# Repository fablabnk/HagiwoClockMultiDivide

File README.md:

This is an attempt to make a PCB version of [Hagiwo's Clock Multi Divide module](https://note.com/solder_state/n/n8907f2f6e8f5).

# Notes / ToDo

- I'm using the schematic symbol for Arduino Nano v3.x, check that this matches my actual Nano
- Change pin order of Eurocad 2x5 pin power symbol
- Update screw hole positions on panel template - mine fall between two rail screw holes
    - centre is: 3mm down from edge, 5.08mm across from edge, 3.2 in diameter, seems correct

## Diodes and voltage protection

Which diodes protect against which things? Original text says that the circuit:
1. Does not break due to overvoltage
2. Does not break due to negative voltage
3. Does not break due to overcurrent
4. External clock does not enter the internal clock output
5. Internal clock output does not enter the external clock input
But which diodes do which things?

These diodes are there for protecting the arduino if you plug something in that sends voltages it can’t handle.
Everything negative will go to ground thru one set of diodes, everything over 5V will go to the 5V rail thru the other set.
Out has only one diode because there is already one on pin D13.

## Power

- Arduino is given VIN of 12V? Or is it somehow powered from the 5V rail?
- I notice Higawo uses a 16 pin connector
- But Arduino Nano operating range is quoted as 7-12V
- Should we connect capacitors to the +-12V power connector rails?

## Updating the schematic

There were some small issues with the original Hagiwo schematic. I made the following changes in my KiCad schematic:
- in the External Clock In section, there should be a dot connecting two vertical BAT43 diodes
According to the discussion [here](https://lookmumnocomputer.discourse.group/t/arduino-clock-multiple-divider/2612/3), for the Master Clock Out section:
- The initial diode after Arduino pin D13 should be a small signal diode (IN4148 or similiar)
- The SchottKey diode following the 470 Ohm resistor should actually come before the resistor

## PCB Issues

- My SPDT switch is not board mountable and will need to be wired to the board instead. So I used the footprint "TerminalBlock:TerminalBlock_bornier-3_P5.08mm"
- The Arduino nano will be mounted to the front of the PCB using pin headers

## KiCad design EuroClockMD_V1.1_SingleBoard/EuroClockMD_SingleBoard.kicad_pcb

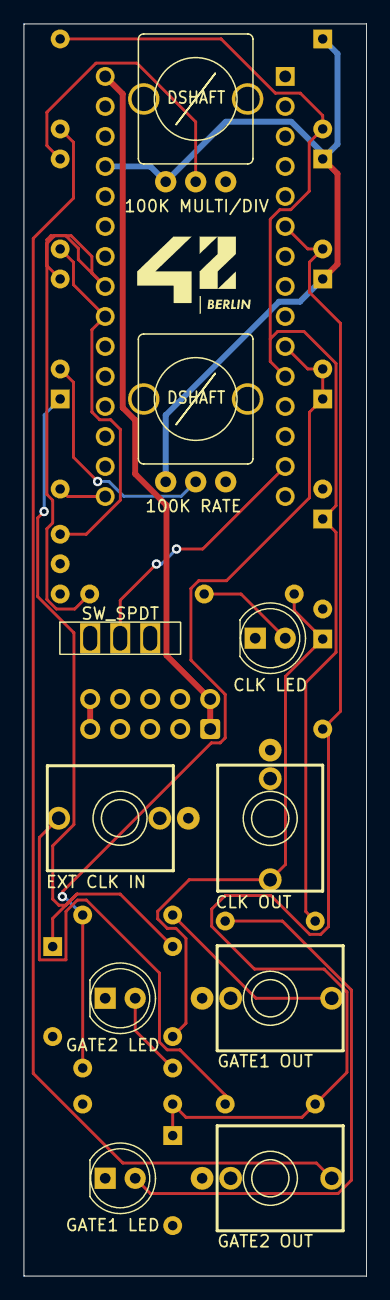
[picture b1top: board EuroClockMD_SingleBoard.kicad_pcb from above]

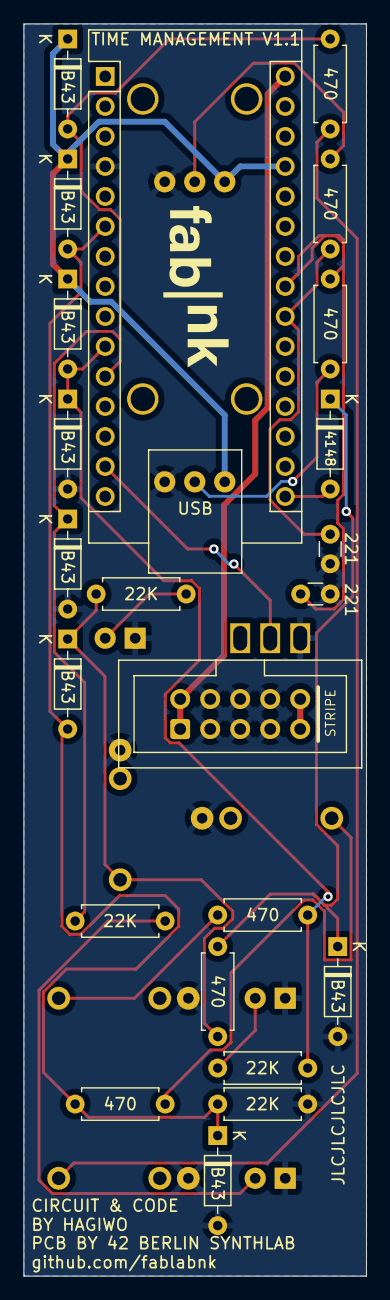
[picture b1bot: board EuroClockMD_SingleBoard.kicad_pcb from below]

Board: 2 copper layers, 29.0 x 106.0 mm, 33 parts (23 on the bottom side), 20 nets.

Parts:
A1: Arduino_Nano_v3.x; Arduino_Nano
C1, C2: 221; C_Disc_D3.0mm_W1.6mm_P2.50mm
D1, D3, D4, D5, D8, D10, D11, D12: B43; D_DO-35_SOD27_P7.62mm_Horizontal
D2: GATE2 LED; LED_D5.0mm
D6: GATE1 LED; LED_D5.0mm
D7: 4148; D_DO-35_SOD27_P7.62mm_Horizontal
D9: CLK LED; LED_D5.0mm
J1: GATE1 OUT; EighthInch_PJ398SM_T_TN_S
J2: GATE2 OUT; EighthInch_PJ398SM_T_TN_S
J3: CLK OUT; EighthInch_PJ398SM_T_TN_S
J4: EXT CLK IN; EighthInch_PJ398SM_T_TN_S
J5: EURO_PWR_2x5; IDC-Header_2x05_P2.54mm_Vertical_Euro_Power_Striped
R1, R3, R4, R6, R7, R9: 470; R_Axial_DIN0207_L6.3mm_D2.5mm_P7.62mm_Horizontal
R2, R5, R8, R10: 22K; R_Axial_DIN0207_L6.3mm_D2.5mm_P7.62mm_Horizontal
RV1: 100K MULTI/DIV; Pot_9mm_DShaft_RemovedPins4_5
RV2: 100K RATE; Pot_9mm_DShaft_RemovedPins4_5
SW1: SW_SPDT; SW_Slide-03_Wuerth-WS-SLTV_10x2.5x6.4_P2.54mm

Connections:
+5V: A1.27 (+5V), D1.1 (K), D4.1 (K), D10.1 (K), RV1.1, RV2.1
GND: A1.4 (GND), C1.2, C2.2, D2.1 (K), D3.2 (A), D5.2 (A), D6.1 (K), D8.2 (A), D9.1 (K), D11.2 (A), J1.S, J2.S, J3.S, J4.S, J5.3 (GND), J5.4 (GND), J5.5 (GND), J5.6 (GND), J5.7 (GND), J5.8 (GND), R10.2, RV1.3, RV2.3, SW1.2 (B)
unnamed: A1.22 (A3), C1.1, R1.2
unnamed: A1.23 (A4), C2.1, R6.2
unnamed: A1.6 (D3), D10.2 (A), D11.1 (K), D12.2 (A), R9.2, R10.1
unnamed: A1.10 (D7), D3.1 (K), D4.2 (A), R2.2, R3.1
unnamed: A1.11 (D8), D1.2 (A), D5.1 (K), R5.2, R7.1
unnamed: A1.14 (D11), SW1.1 (A)
unnamed: A1.16 (D13), D7.2 (A)
unnamed: A1.30 (VIN), J5.1 (+12V), J5.2 (+12V)
unnamed: D2.2 (A), R2.1
unnamed: D6.2 (A), R5.1
unnamed: D7.1 (K), D8.1 (K), R4.1
unnamed: D9.2 (A), R8.1
unnamed: D12.1 (K), J3.T, R4.2, R8.2
unnamed: J1.T, R3.2
unnamed: J2.T, R7.2
unnamed: J4.T, R9.1
unnamed: R1.1, RV1.2
unnamed: R6.1, RV2.2

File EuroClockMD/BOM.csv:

"Reference","Value","Datasheet","Footprint","Qty","DNP"
"A1","Arduino_Nano_v3.x","http://www.mouser.com/pdfdocs/Gravitech_Arduino_Nano3_0.pdf","Module:Arduino_Nano","1",""
"C1,C2","220p","~","Capacitor_THT:C_Disc_D3.0mm_W1.6mm_P2.50mm","2",""
"D1,D3,D4,D5,D8,D10,D11,D12","BAT43","http://www.vishay.com/docs/85660/bat42.pdf","Diode_THT:D_DO-35_SOD27_P7.62mm_Horizontal","8",""
"D2","GATE OUT 1 LED","~","LED_THT:LED_D5.0mm","1",""
"D6","GATE OUT 2 LED","~","LED_THT:LED_D5.0mm","1",""
"D7","IN4148","~","Diode_THT:D_DO-35_SOD27_P7.62mm_Horizontal","1",""
"D9","CLOCK OUT LED","~","LED_THT:LED_D5.0mm","1",""
"J1","GATE OUT 1","~","Eurocad:PJ301M-12_T_S","1",""
"J2","GATE OUT 2","~","Eurocad:PJ301M-12_T_S","1",""
"J3","CLOCK OUT","~","Eurocad:PJ301M-12_T_S","1",""
"J4","EXT CLK IN","~","Eurocad:PJ301M-12_T_S","1",""
"J5","EURO_PWR_2x5","","Connector_IDC:IDC-Header_2x05_P2.54mm_Vertical","1",""
"J6","Conn_01x15_Pin_Left","~","Connector_PinHeader_2.54mm:PinHeader_1x15_P2.54mm_Vertical","1",""
"J7","Conn_01x15_Socket_Left","~","Connector_PinSocket_2.54mm:PinSocket_1x15_P2.54mm_Vertical","1",""
"J8","Conn_01x15_Socket_Right","~","Connector_PinSocket_2.54mm:PinSocket_1x15_P2.54mm_Vertical","1",""
"J9","Conn_01x15_Pin_Right","~","Connector_PinHeader_2.54mm:PinHeader_1x15_P2.54mm_Vertical","1",""
"R1,R3,R4,R6,R7,R9","470","~","Resistor_THT:R_Axial_DIN0207_L6.3mm_D2.5mm_P7.62mm_Horizontal","6",""
"R2,R5,R8,R10","22K","~","Resistor_THT:R_Axial_DIN0207_L6.3mm_D2.5mm_P7.62mm_Horizontal","4",""
"RV1","100K MULTI/DIV","~","Eurocad:Alpha9mmPot","1",""
"RV2","100K RATE","~","Eurocad:Alpha9mmPot","1",""
"SW1","SW_SPDT (Internal Pullup)","~","Button_Switch_THT:SW_Slide-03_Wuerth-WS-SLTV_10x2.5x6.4_P2.54mm","1",""

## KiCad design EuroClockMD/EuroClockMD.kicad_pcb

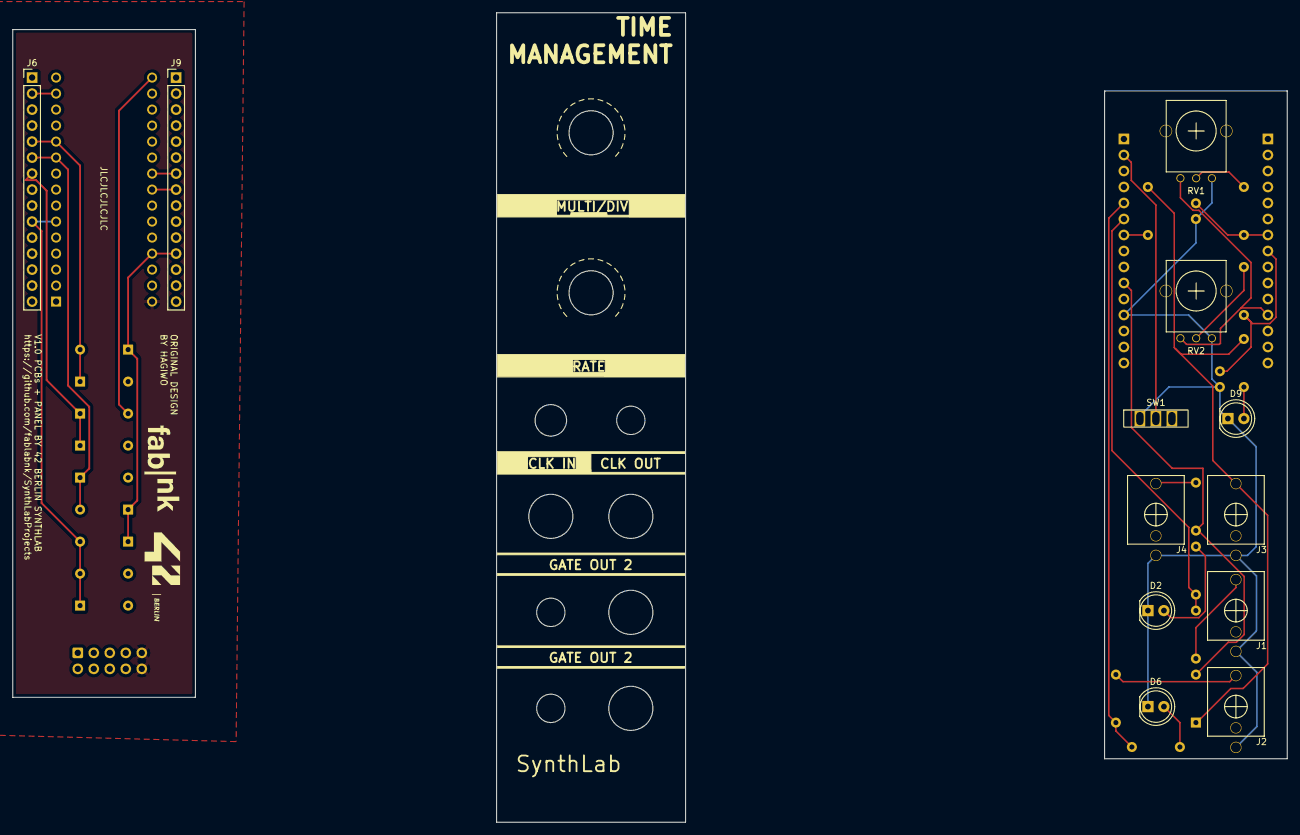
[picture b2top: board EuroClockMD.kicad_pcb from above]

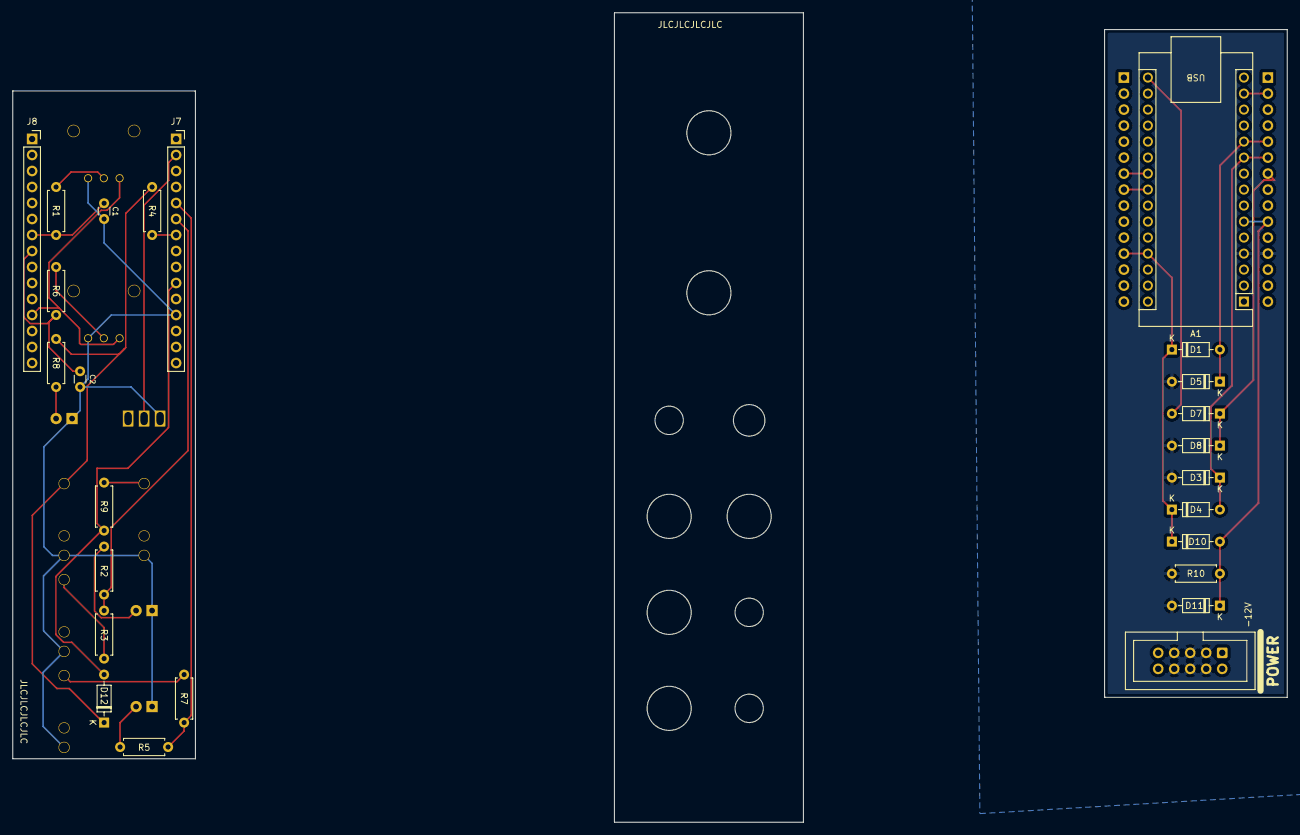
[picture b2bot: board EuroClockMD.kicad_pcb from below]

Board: 2 copper layers, 202.3 x 128.5 mm, 37 parts (25 on the bottom side), 11 nets.

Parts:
A1: Arduino_Nano_v3.x; Arduino_Nano
C1, C2: 220p; C_Disc_D3.0mm_W1.6mm_P2.50mm
D1, D3, D4, D5, D8, D10, D11, D12: BAT43; D_DO-35_SOD27_P7.62mm_Horizontal
D2: GATE OUT 1 LED; LED_D5.0mm
D6: GATE OUT 2 LED; LED_D5.0mm
D7: IN4148; D_DO-35_SOD27_P7.62mm_Horizontal
D9: CLOCK OUT LED; LED_D5.0mm
J1: GATE OUT 1; PJ301M-12_T_S
J2: GATE OUT 2; PJ301M-12_T_S
J3: CLOCK OUT; PJ301M-12_T_S
J4: EXT CLK IN; PJ301M-12_T_S
J5: EURO_PWR_2x5; Pins_2x05_2.54mm_TH_EurorackPower_Shrouded
J6: Conn_01x15_Pin_Left; PinHeader_1x15_P2.54mm_Vertical
J7: Conn_01x15_Socket_Left; PinSocket_1x15_P2.54mm_Vertical
J8: Conn_01x15_Socket_Right; PinSocket_1x15_P2.54mm_Vertical
J9: Conn_01x15_Pin_Right; PinHeader_1x15_P2.54mm_Vertical
R1, R3, R4, R6, R7, R9: 470; R_Axial_DIN0207_L6.3mm_D2.5mm_P7.62mm_Horizontal
R2, R5, R8, R10: 22K; R_Axial_DIN0207_L6.3mm_D2.5mm_P7.62mm_Horizontal
RV1: 100K MULTI/DIV; Alpha9mmPot
RV2: 100K RATE; Alpha9mmPot
SW1: SW_SPDT (Internal Pullup); SW_Slide-03_Wuerth-WS-SLTV_10x2.5x6.4_P2.54mm

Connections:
GND: A1.4 (GND), D3.2 (A), D5.2 (A), D8.2 (A), D11.2 (A), J5.3 (GND), J5.4 (GND), J5.5 (GND), J5.6 (GND), J5.7 (GND), J5.8 (GND), J6.12, R10.2
unnamed: A1.16 (D13), D7.2 (A)
unnamed: A1.30 (VIN), J5.9 (+12V), J5.10 (+12V)
P1: A1.22 (A3), J9.7
P2: A1.23 (A4), J9.8
P3: A1.6 (D3), D10.2 (A), D11.1 (K), J6.10, R10.1
P4: A1.14 (D11), J6.2
P5: A1.10 (D7), D3.1 (K), D4.2 (A), J6.6
P5V: A1.27 (+5V), D1.1 (K), D4.1 (K), D10.1 (K), J9.12
P6: A1.11 (D8), D1.2 (A), D5.1 (K), J6.5
P7: D7.1 (K), D8.1 (K), J6.7

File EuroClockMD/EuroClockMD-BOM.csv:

"Id";"Designator";"Footprint";"Quantity";"Designation";"Supplier and ref";
1;"REF**,REF**";"Eurorack_Panel_ScrewHole_Oval";2;"Eurorack_Panel_ScrewHole_Oval";;;
2;"J4";"PJ301M-12_T_S";1;"EXT CLK IN";;;
3;"D9";"LED_D5.0mm";1;"CLOCK OUT LED";;;
4;"J9";"PinHeader_1x15_P2.54mm_Vertical";1;"Conn_01x15_Pin_Right";;;
5;"J2";"PJ301M-12_T_S";1;"GATE OUT 2";;;
6;"J3";"PJ301M-12_T_S";1;"CLOCK OUT";;;
7;"SW1";"SW_Slide-03_Wuerth-WS-SLTV_10x2.5x6.4_P2.54mm";1;"SW_SPDT (Internal Pullup)";;;
8;"D6";"LED_D5.0mm";1;"GATE OUT 2 LED";;;
9;"D2";"LED_D5.0mm";1;"GATE OUT 1 LED";;;
10;"RV1";"Alpha9mmPot";1;"100K MULTI/DIV";;;
11;"RV2";"Alpha9mmPot";1;"100K RATE";;;
12;"J1";"PJ301M-12_T_S";1;"GATE OUT 1";;;
13;"J6";"PinHeader_1x15_P2.54mm_Vertical";1;"Conn_01x15_Pin_Left";;;
14;"R1,R4,R9,R6,R3,R7";"R_Axial_DIN0207_L6.3mm_D2.5mm_P7.62mm_Horizontal";6;"470";;;
15;"D8,D4,D10,D12,D5,D3,D1,D11";"D_DO-35_SOD27_P7.62mm_Horizontal";8;"BAT43";;;
16;"J8";"PinSocket_1x15_P2.54mm_Vertical";1;"Conn_01x15_Socket_Right";;;
17;"J7";"PinSocket_1x15_P2.54mm_Vertical";1;"Conn_01x15_Socket_Left";;;
18;"R8,R2,R5,R10";"R_Axial_DIN0207_L6.3mm_D2.5mm_P7.62mm_Horizontal";4;"22K";;;
19;"D7";"D_DO-35_SOD27_P7.62mm_Horizontal";1;"IN4148";;;
20;"C2,C1";"C_Disc_D3.0mm_W1.6mm_P2.50mm";2;"220p";;;
21;"J5";"IDC-Header_2x05_P2.54mm_Vertical";1;"EURO_PWR_2x5";;;
22;"A1";"Arduino_Nano";1;"Arduino_Nano_v3.x";;;

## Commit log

2024-04-03 First sketch of schematic completed with footprints
2024-06-01 pushing latest updates
2024-06-01 retraced EuroClockMD-Pin and moved holes in EuroClockMD-panel
2024-06-20 added the code to the repo
    also translated the japanese comments
2024-07-13 Completed v1.1 - single board version with correct power header orientation, ground plane and corrected panel holes sizes (LEDs)
2024-08-13 latest updates
2024-12-12 updating after a while dormant
